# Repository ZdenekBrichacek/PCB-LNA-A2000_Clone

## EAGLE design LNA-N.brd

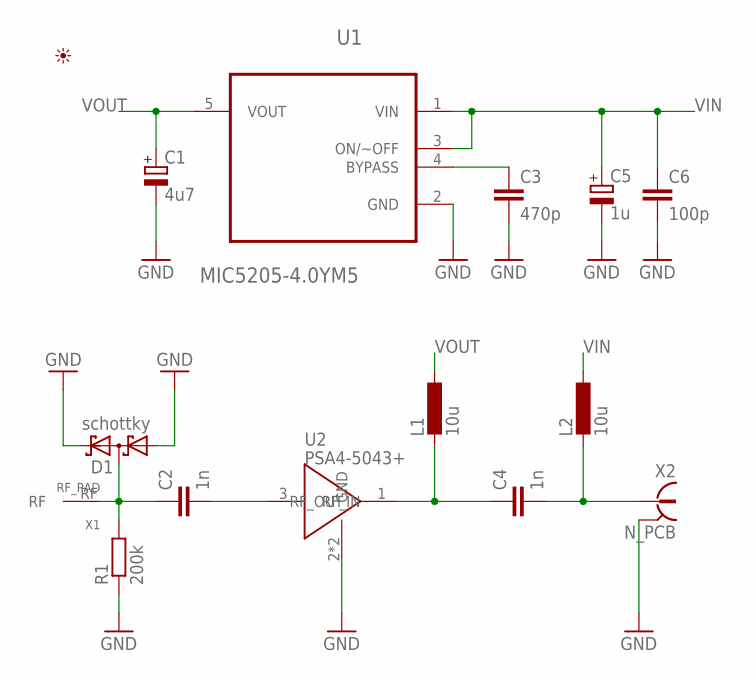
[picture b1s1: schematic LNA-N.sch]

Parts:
C1: 4u7; SMC_A
C2, C4: 1n; C0805
C3: 470p; C0603
C5: 1u; SMC_A
C6: 100p; C0603
D1: schottky; SOT23
L1, L2: 10u; L2012C
R1: 200k; R0805
U1: MIC5205-4.0YM5; SOT95P280X145-5N
U2: PSA4-5043+; SOT343
U$1: PICTO_1
X1: RF_PAD
X2: N_PCB

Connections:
GND: C1.-, C3.2, C5.-, C6.2, D1.1 (A1), D1.2 (C2), R1.1, U1.2 (GND), U2.2 (GND), U2.4 (GND), X2.2, X2.3 (2), X2.4 (2), X2.5 (2)
unnamed: C3.1, U1.4 (BYPASS)
unnamed: C2.2, U2.3 (RF_IN)
unnamed: C4.1, L1.2, U2.1 (RF_OUT)
RF_IN: C2.1, D1.3 (C1A2), R1.2, X1.RF
RF_OUT: C4.2, L2.2, X2.1
VIN: C5.+, C6.1, L2.1, U1.1 (VIN), U1.3 (ON/~OFF)
VOUT: C1.+, L1.1, U1.5 (VOUT)

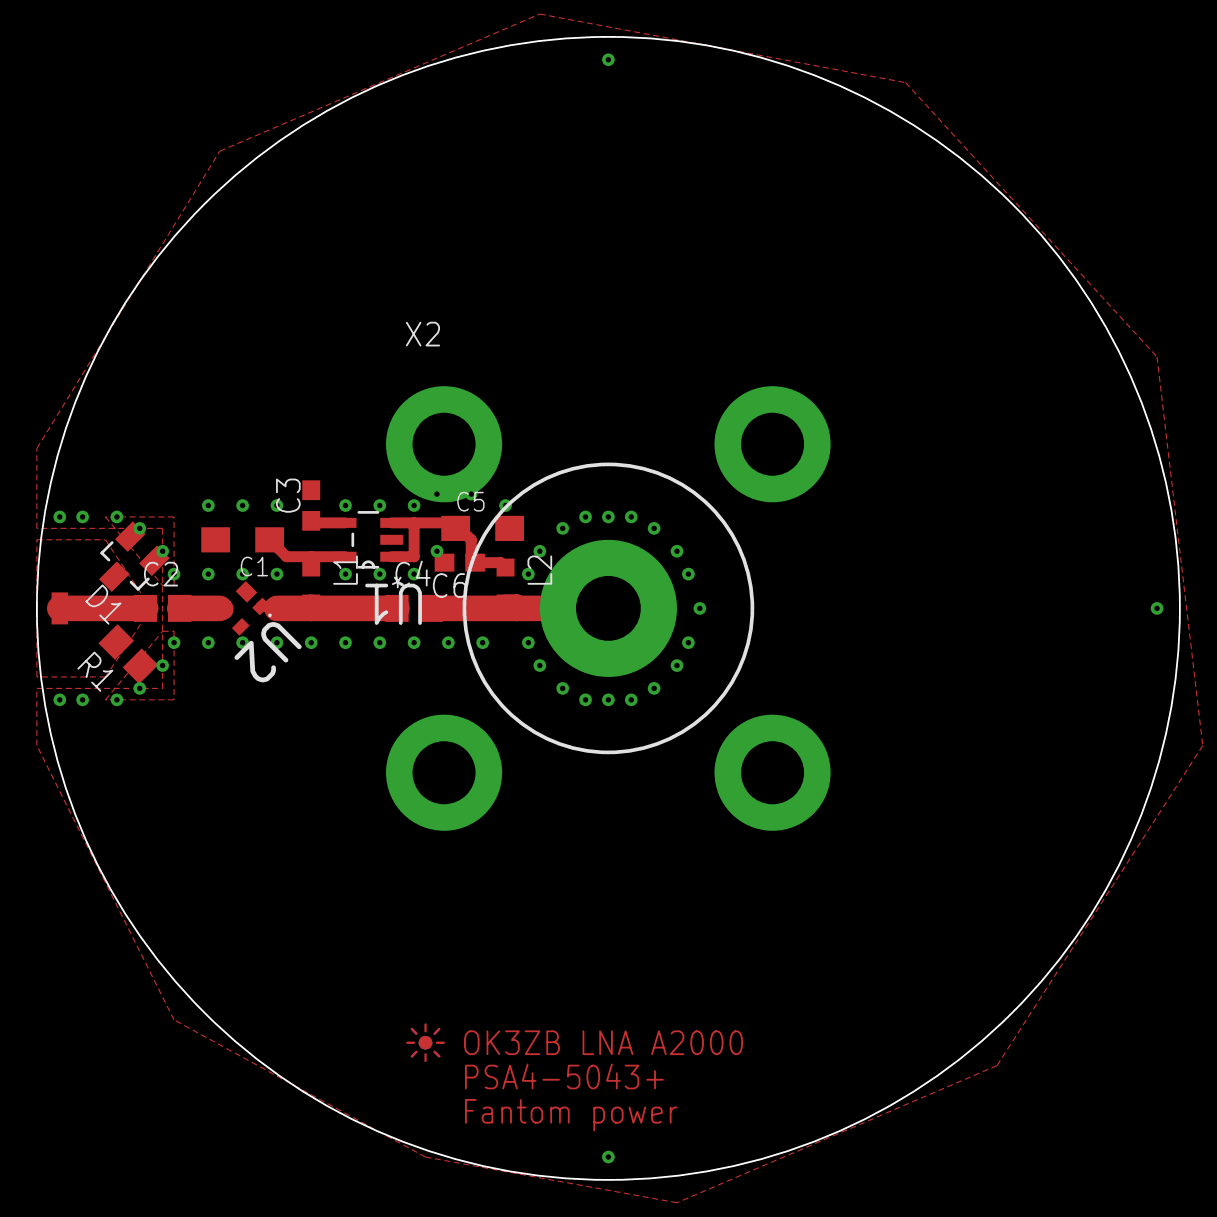
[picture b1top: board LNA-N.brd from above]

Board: 2 copper layers, 63.5 x 63.5 mm, 15 parts (0 on the bottom side), 8 nets.

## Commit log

2017-10-10 :neckbeard: Added .gitattributes & .gitignore files
2017-10-10 Initial version
